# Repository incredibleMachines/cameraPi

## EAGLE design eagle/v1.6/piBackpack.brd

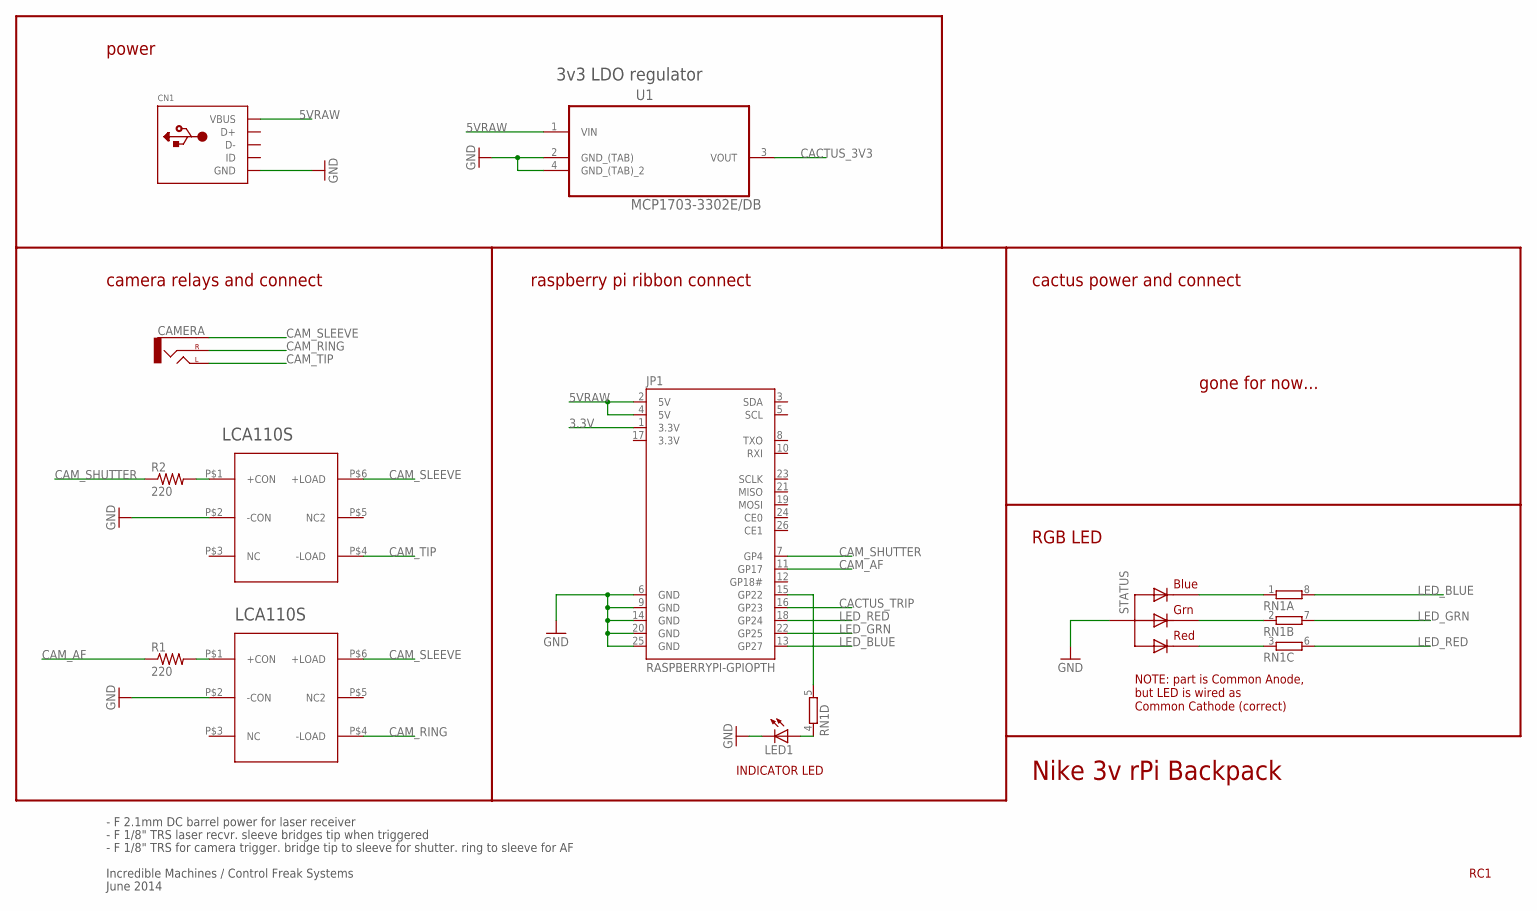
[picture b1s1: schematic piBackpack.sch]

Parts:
CAMERA: AUDIO-JACKPTH; AUDIO-JACK
CN1: USBMOLEX; USB-MINIB-THM-MOLEX
JP1: RASPBERRYPI-GPIOPTH; 2X13-SHROUDED
LCA110S, LCA110S1: LCA110S; 6-SMD
LED1: LED3MM
R1, R2: 220; 0204/5
RN1: 4R-NEXBS8V; EXBS8V
STATUS: RGBLED_CA-5MM; LED5MMRGB
U1: MCP1703-3302E/DB; SOT230P700X180-4N

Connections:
3.3V: JP1.1 (3.3V), JP1.17 (3.3V)
5VRAW: CN1.VBUS, JP1.2 (5V), JP1.4 (5V), U1.1 (VIN)
CACTUS_3V3: U1.3 (VOUT)
CACTUS_TRIP: JP1.16 (GP23)
CAM_AF: JP1.11 (GP17), R1.1
CAM_RING: CAMERA.RING (RIGHT), LCA110S.P$4 (-LOAD)
CAM_SHUTTER: JP1.7 (GP4), R2.1
CAM_SLEEVE: CAMERA.SLEEVE, LCA110S.P$6 (+LOAD), LCA110S1.P$6 (+LOAD)
CAM_TIP: CAMERA.TIP (LEFT), LCA110S1.P$4 (-LOAD)
GND: CN1.GND, JP1.6 (GND), JP1.9 (GND), JP1.14 (GND), JP1.20 (GND), JP1.25 (GND), LCA110S.P$2 (-CON), LCA110S1.P$2 (-CON), LED1.K (C), STATUS.2 (VCC), U1.2 (GND_(TAB)), U1.4 (GND_(TAB)_2)
LED_BLUE: JP1.13 (GP27), RN1.8 (2)
LED_GRN: JP1.22 (GP25), RN1.7 (2)
LED_RED: JP1.18 (GP24), RN1.6 (2)
unnamed: RN1.1, STATUS.4 (BLUE)
unnamed: RN1.2 (1), STATUS.3 (GREEN)
unnamed: RN1.3 (1), STATUS.1 (RED)
unnamed: JP1.15 (GP22), RN1.5 (2)
unnamed: LED1.A, RN1.4 (1)
unnamed: LCA110S.P$1 (+CON), R1.2
unnamed: LCA110S1.P$1 (+CON), R2.2

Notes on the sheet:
Nike 3v rPi Backpack
Incredible Machines / Control Freak Systems
June 2014
- F 2.1mm DC barrel power for laser receiver
- F 1/8" TRS laser recvr. sleeve bridges tip when triggered
- F 1/8" TRS for camera trigger. bridge tip to sleeve for shutter. ring to sleeve for AF
NOTE: part is Common Anode, but LED is wired as Common Cathode (correct)
raspberry pi ribbon connect
camera relays and connect
RGB LED
cactus power and connect
RC1
INDICATOR LED
power
3v3 LDO regulator
LCA110S
gone for now...

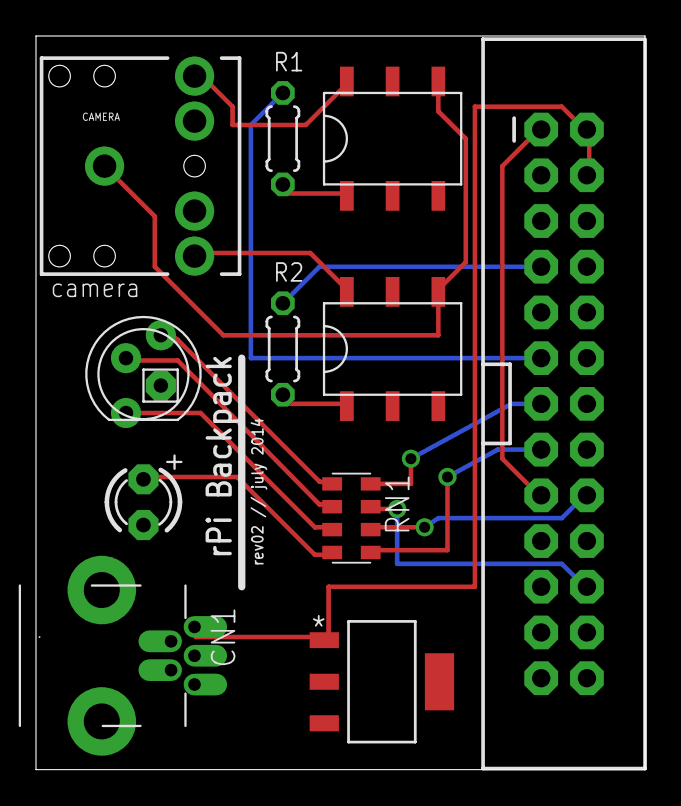
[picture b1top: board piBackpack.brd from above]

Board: 2 copper layers, 33.8 x 40.8 mm, 11 parts (0 on the bottom side), 18 nets.

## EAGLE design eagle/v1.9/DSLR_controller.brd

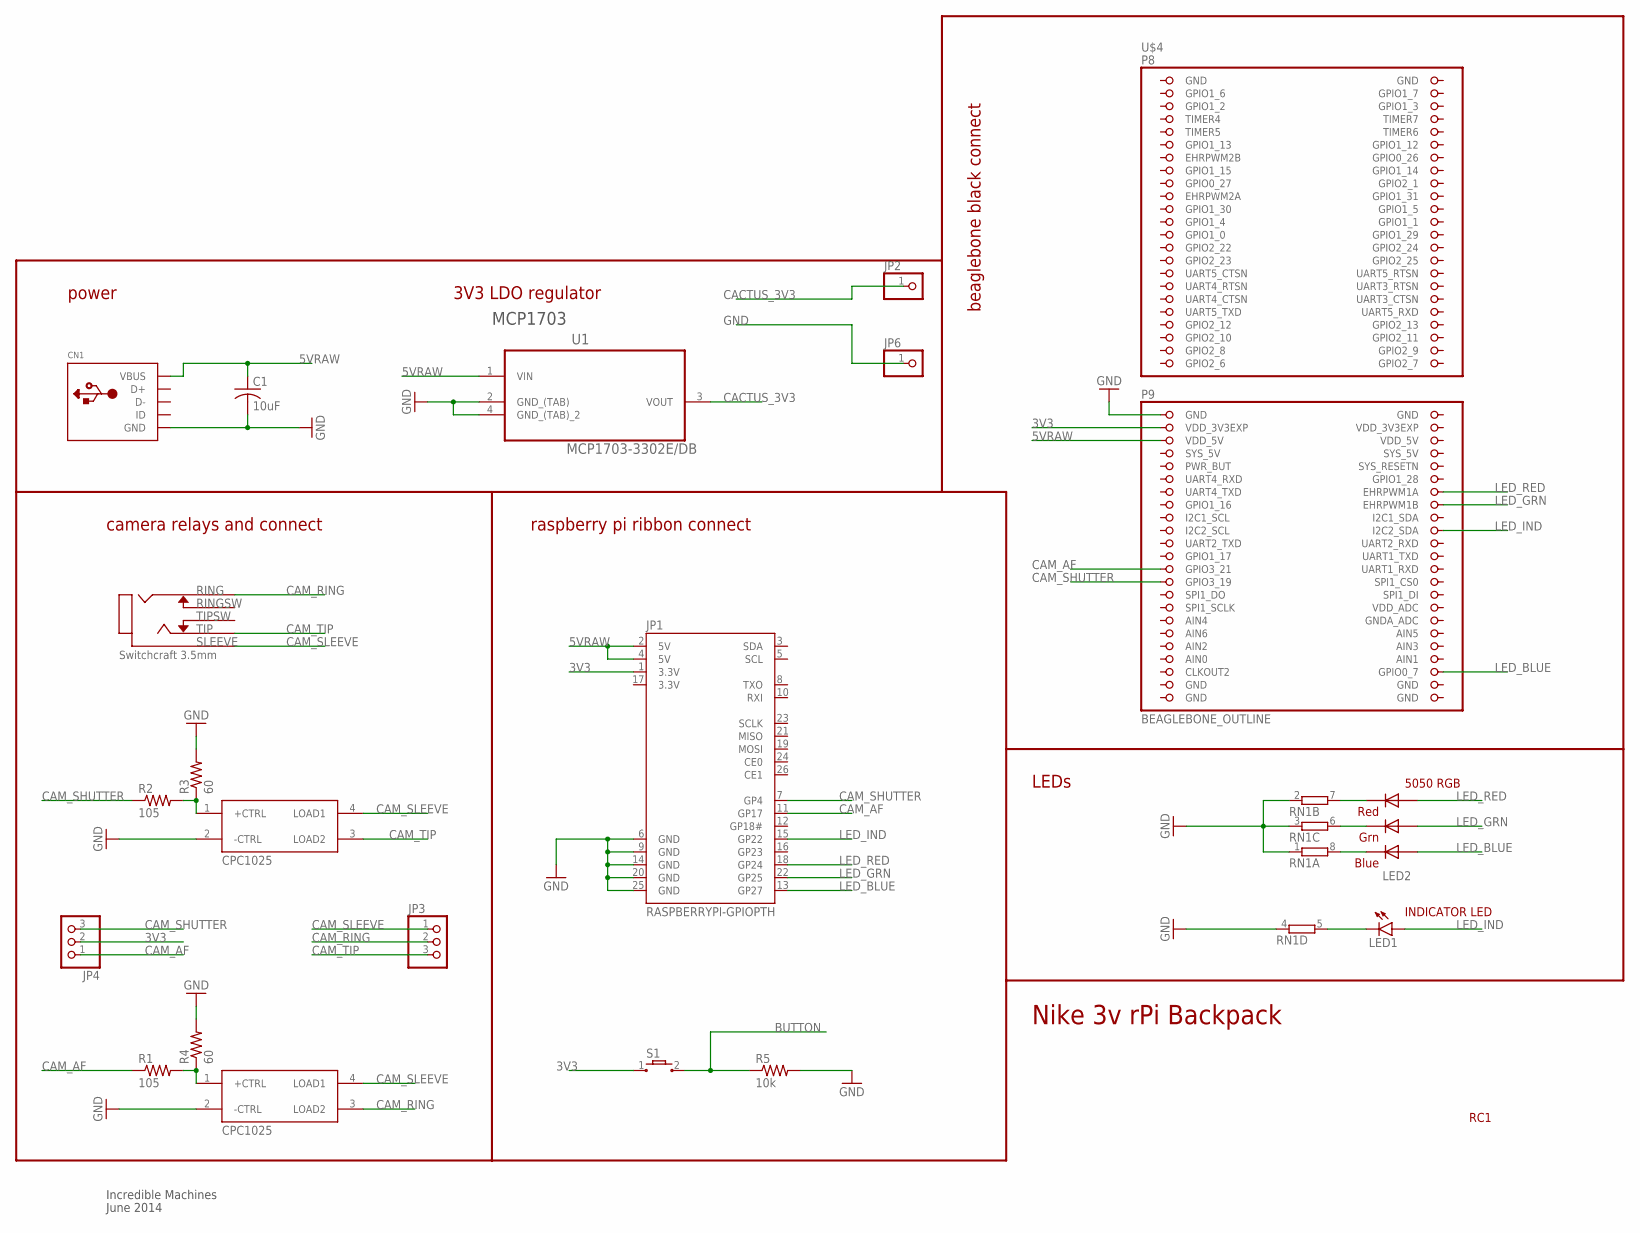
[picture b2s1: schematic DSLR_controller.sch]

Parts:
C1: 10uF; C1206K
CN1: USBMOLEX; USB-MINIB-THM-MOLEX
JP1: RASPBERRYPI-GPIOPTH; 2X13-SHROUDED
JP2, JP6: PINHD-1X1CB; 1X01-CLEANBIG
JP3, JP4: PINHD-1X3CB; 1X03-CLEANBIG
LED1: LED1206; LED-1206
LED2: RGBLED5050
R1, R2: 105; R1206
R3, R4: 60; R1206
R5: 10k; R1206
RN1: 4R-NEXBS8V; EXBS8V
S1: TL3302-G; TL3302_GULL_WING
U1: MCP1703-3302E/DB; SOT230P700X180-4N
U$1: SWTCHCRFT_3.5JACK5-JACK-SMD; 4-JACK-SMD
U$2, U$3: CPC1025_OPTORELAY; 4-OPTORELAY
U$4: BEAGLEBONE_OUTLINE; BEAGLEBONE_SHIELD

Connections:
3.3V: JP1.17 (3.3V)
3V3: JP1.1 (3.3V), JP4.2, S1.1, U$4.49 (VDD_3V3EXP)
5VRAW: C1.1, CN1.VBUS, JP1.2 (5V), JP1.4 (5V), U1.1 (VIN), U$4.51 (VDD_5V)
AIN0: U$4.85 (AIN0)
BUTTON: R5.1, S1.2
CACTUS_3V3: JP2.1, U1.3 (VOUT)
CAM_AF: JP1.11 (GP17), JP4.1, R1.1, U$4.71 (GPIO3_21)
CAM_RING: JP3.2, U$1.2, U$2.3 (LOAD2)
CAM_SHUTTER: JP1.7 (GP4), JP4.3, R2.1, U$4.73 (GPIO3_19)
CAM_SLEEVE: JP3.1, U$1.1, U$2.4 (LOAD1), U$3.4 (LOAD1)
CAM_TIP: JP3.3, U$1.3, U$3.3 (LOAD2)
GND: C1.2, CN1.GND, JP1.6 (GND), JP1.9 (GND), JP1.14 (GND), JP1.20 (GND), JP1.25 (GND), JP6.1, R3.2, R4.2, R5.2, RN1.1, RN1.2 (1), RN1.3 (1), RN1.4 (1), U1.2 (GND_(TAB)), U1.4 (GND_(TAB)_2), U$2.2 (-CTRL), U$3.2 (-CTRL), U$4.1 (GND), U$4.2 (GND), U$4.47 (GND), U$4.48 (GND), U$4.89 (GND), U$4.90 (GND), U$4.91 (GND), U$4.92 (GND)
LED_BLUE: JP1.13 (GP27), LED2.3 (BLUE_A), U$4.88 (GPIO0_7)
LED_GRN: JP1.22 (GP25), LED2.1 (GREEN_A), U$4.62 (EHRPWM1B)
LED_IND: JP1.15 (GP22), LED1.A, U$4.66 (I2C2_SDA)
LED_RED: JP1.18 (GP24), LED2.2 (RED_A), U$4.60 (EHRPWM1A)
unnamed: LED2.6 (GREEN_C), RN1.6 (2)
unnamed: LED2.5 (RED_C), RN1.7 (2)
unnamed: LED2.4 (BLUE_C), RN1.8 (2)
unnamed: LED1.C, RN1.5 (2)
unnamed: R1.2, R4.1, U$2.1 (+CTRL)
unnamed: R2.2, R3.1, U$3.1 (+CTRL)
SYS_5V: U$4.53 (SYS_5V)
VDD_3V3EXP: U$4.50 (VDD_3V3EXP)
VDD_5V: U$4.52 (VDD_5V)

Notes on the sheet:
Nike 3v rPi Backpack
Incredible Machines
June 2014
raspberry pi ribbon connect
camera relays and connect
LEDs
RC1
INDICATOR LED
power
MCP1703
beaglebone black connect
5050 RGB
3V3 LDO regulator

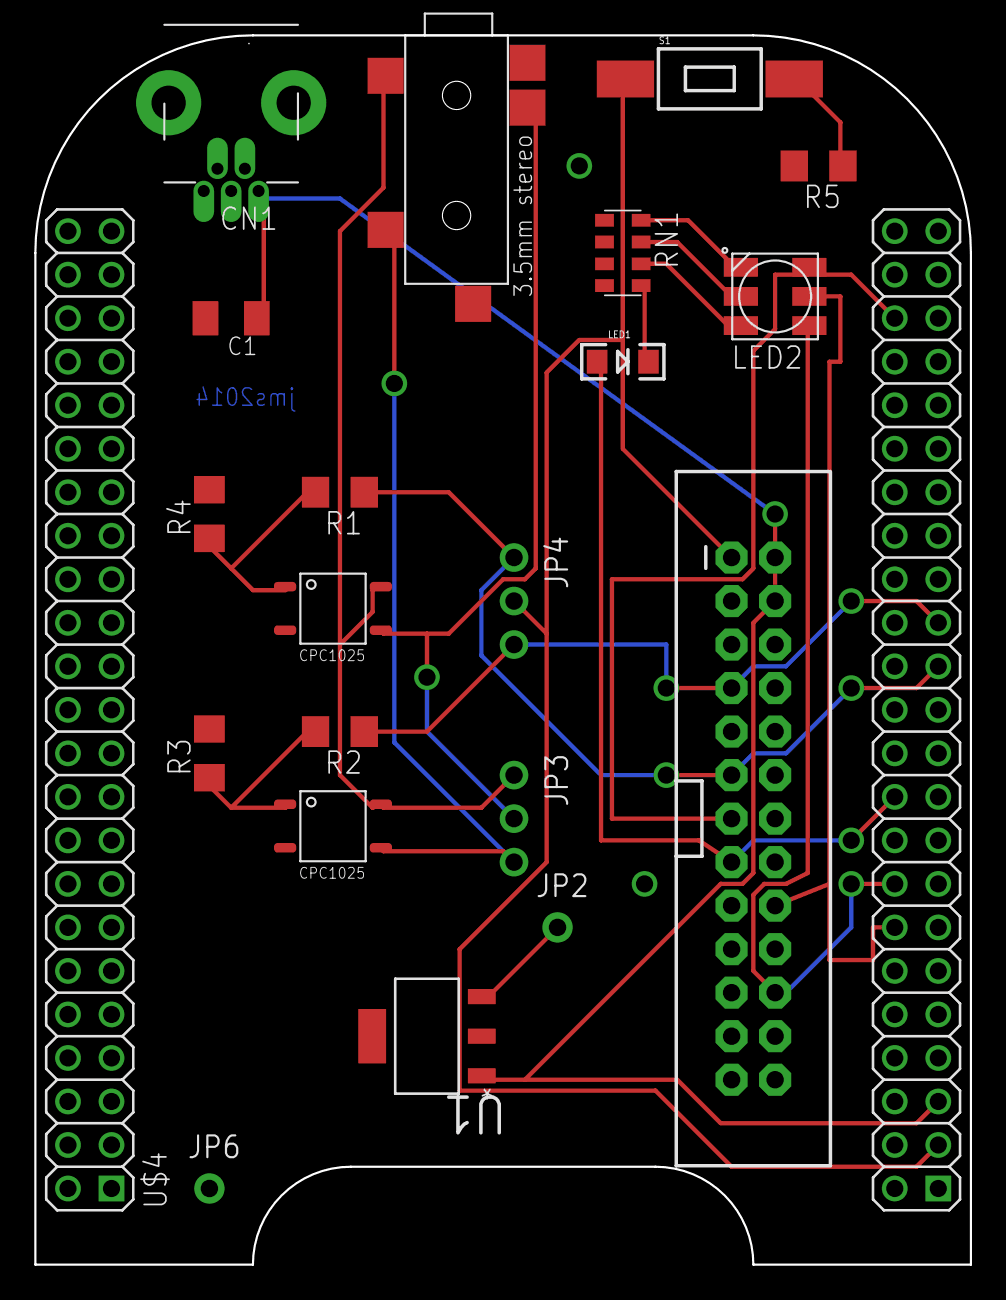
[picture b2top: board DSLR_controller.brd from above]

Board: 2 copper layers, 54.6 x 71.8 mm, 21 parts (0 on the bottom side), 20 nets.

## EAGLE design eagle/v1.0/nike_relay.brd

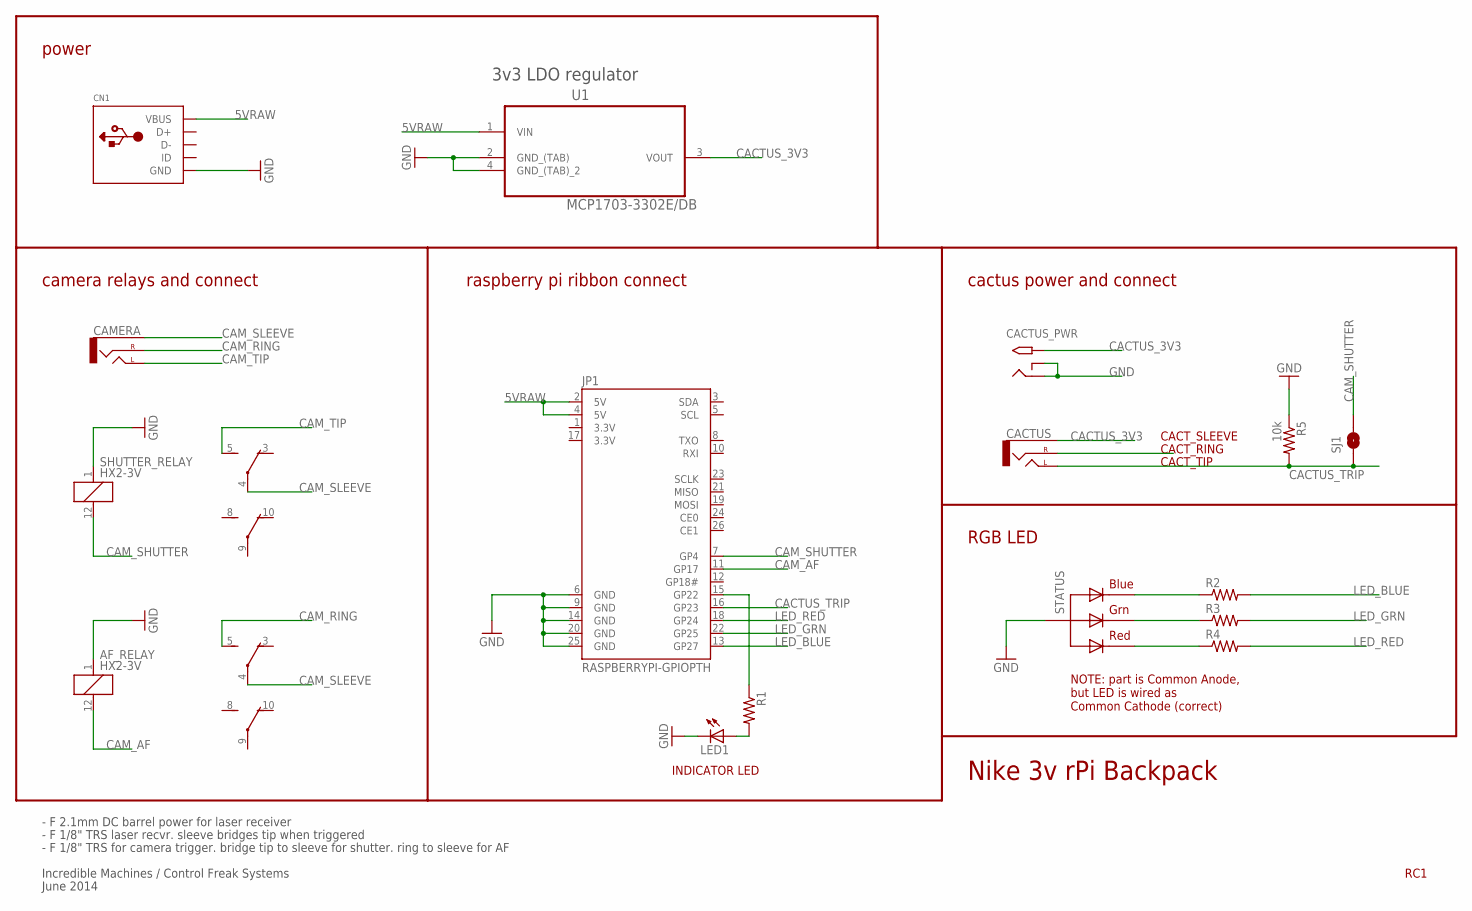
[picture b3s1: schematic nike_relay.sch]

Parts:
AF_RELAY: HX2-3V; HX
CACTUS: AUDIO-JACKPTH; AUDIO-JACK
CACTUS_PWR: 2.1MMJACKTHM; PJ-102A
CAMERA: AUDIO-JACKPTH; AUDIO-JACK
CN1: USBMOLEX; USB-MINIB-THM-MOLEX
JP1: RASPBERRYPI-GPIOPTH; 2X13-SHROUDED
LED1: LED3MM
R1, R2, R3, R4: R-US_0204/5; 0204/5
R5: 10k; 0204/5
SHUTTER_RELAY: HX2-3V; HX
SJ1: SOLDERJUMPER-OLDNO; SJ_2S-NO
STATUS: RGBLED_CA-5MM; LED5MMRGB
U1: MCP1703-3302E/DB; SOT230P700X180-4N

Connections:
3.3V: JP1.1 (3.3V), JP1.17 (3.3V)
5VRAW: CN1.VBUS, JP1.2 (5V), JP1.4 (5V), U1.1 (VIN)
CACTUS_3V3: CACTUS.SLEEVE, CACTUS_PWR.TIP, U1.3 (VOUT)
CACTUS_TRIP: CACTUS.TIP (LEFT), JP1.16 (GP23), R5.2, SJ1.1
CACT_RING: CACTUS.RING (RIGHT)
CAM_AF: AF_RELAY.12 (2), JP1.11 (GP17)
CAM_RING: AF_RELAY.5 (S), CAMERA.RING (RIGHT)
CAM_SHUTTER: JP1.7 (GP4), SHUTTER_RELAY.12 (2), SJ1.2
CAM_SLEEVE: AF_RELAY.4, CAMERA.SLEEVE, SHUTTER_RELAY.4
CAM_TIP: CAMERA.TIP (LEFT), SHUTTER_RELAY.5 (S)
GND: AF_RELAY.1, CACTUS_PWR.RING, CACTUS_PWR.RING_SW, CN1.GND, JP1.6 (GND), JP1.9 (GND), JP1.14 (GND), JP1.20 (GND), JP1.25 (GND), LED1.K (C), R5.1, SHUTTER_RELAY.1, STATUS.2 (VCC), U1.2 (GND_(TAB)), U1.4 (GND_(TAB)_2)
LED_BLUE: JP1.13 (GP27), R2.2
LED_GRN: JP1.22 (GP25), R3.2
LED_RED: JP1.18 (GP24), R4.2
unnamed: R2.1, STATUS.4 (BLUE)
unnamed: R3.1, STATUS.3 (GREEN)
unnamed: R4.1, STATUS.1 (RED)
unnamed: JP1.15 (GP22), R1.1
unnamed: LED1.A, R1.2

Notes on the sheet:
Nike 3v rPi Backpack
Incredible Machines / Control Freak Systems
June 2014
- F 2.1mm DC barrel power for laser receiver
- F 1/8" TRS laser recvr. sleeve bridges tip when triggered
- F 1/8" TRS for camera trigger. bridge tip to sleeve for shutter. ring to sleeve for AF
CACT_SLEEVE
CACT_TIP
CACT_RING
NOTE: part is Common Anode, but LED is wired as Common Cathode (correct)
raspberry pi ribbon connect
camera relays and connect
RGB LED
cactus power and connect
RC1
INDICATOR LED
power
3v3 LDO regulator

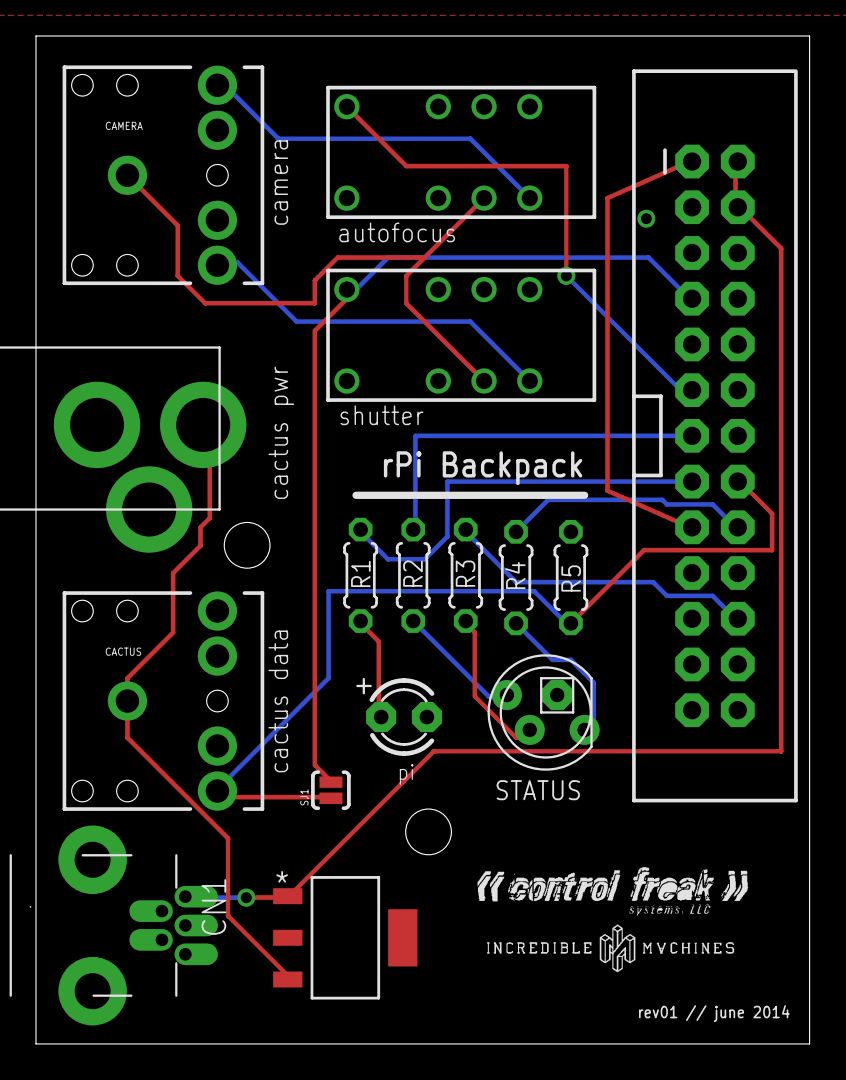
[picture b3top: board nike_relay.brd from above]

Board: 2 copper layers, 43.0 x 56.0 mm, 16 parts (0 on the bottom side), 18 nets.

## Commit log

2014-06-06 Adding Basic ignore strategies
2014-06-06 Adding .gitignore
2014-06-06 Adding all the files
2014-06-07 added all eagle files for rPi backpack
2014-06-07 updating ignore to include .jpg files
2014-06-07 Various Changes still in beta form - image downloading, camera control, gpio functionality
    Beta state for various server implimentations listed below. All these files are super ugly and need lots of work, don't judge.
    CameraControl to sync w. camera via usb and listen for changes in order to capture images and post to download server.
    Download to receive images via express to process and name files as they come into our server.
    Minor mods to gpio2.js
2014-06-07 removing bunk imageDownload folder and package
2014-06-07 removing stupid RTF File
2014-06-07 adding restore instructions, should probably be converted to a readme
2014-06-07 enabling download and trigger apps to run concurrently, modifying camera controls to support this functionality
2014-06-07 created laser prototype folder
2014-06-08 laser functionality proven. run node laser.js to see laser hit shutter pin and light LED when triggered. Trigger buffer time implemented.
2014-06-08 Rearranging folder structures adding camera http server functionality
2014-06-08 reformatting naming of laser trigger
2014-06-08 Initial browser commit App for sending out camera settings
2014-06-08 deleting bunk file
2014-06-08 adding .mov
2014-06-08 removing bunk .mov files
2014-06-08 adding in captureAll.js - a test to try all GPIO pin activity using asynchronous interrupts. package.json now includes onoff package
2014-06-08 Working drop downs for all camera settings
2014-06-08 Adding support for Camera API http server and Capture EOSSerialCapture and report
    This code still needs to test the http posting etc once the browser app is ready to rock. additionally still needs camera wake up functionality
2014-06-08 updated laser.js to use onoff, captureALL test added, packages all include onoff now
2014-06-08 fixing capture to run after get is recieved
2014-06-08 updated capture.js to use the onoff npm and updated package.json to match
2014-06-08 Camera Management
    P C# Please enter the commit message for your changes. Lines starting
2014-06-08 Working Camera naming off MongoDB
2014-06-08 port switch to 80
2014-06-08 I lied, setting back to 3000
2014-06-08 RC2 - pi_code
    all correct IP addresses in (show addys)
    updated camera, capture, laser files, packages
    refactored folders
2014-06-09 updating RC2 with all files
2014-06-09 update capture package
2014-06-09 Arm call /arm posts camera info _id, camera_id, address, serial :wq
2014-06-09 Sending get request for setting camera values
2014-06-09 Sends set and get commands to pi Gets settings on load, sets settings when saved individually
2014-06-09 Working check for ip changes, new serial numbers on camera sign on
2014-06-09 Adding trigger updates to browser api also updating capture to get IP address every time.
2014-06-09 quick fix to limit multiple socket connections
2014-06-09 Working camera settings for testing
2014-06-09 pi_code updates and stablization
2014-06-09 Fixed wrong characters
2014-06-09 updating browser_server ip address
2014-06-09 Fixed http requests
2014-06-09 Changed pi route to '/camera'
2014-06-09 organizing utils folder
2014-06-09 updated camera.js to use GPIO lib to control AF pin for waking the camera up on startup and serialID failure
2014-06-09 updated IP addresses to TRUE IPs, worked on allGpio code
2014-06-09 adding git pull functionality to camera, adding gitpull.sh script
2014-06-09 Updating sh path
2014-06-09 Working database Correct database queries and calls for all timing and camera settings, has laser data in camera object :wq
2014-06-10 updating git pull
2014-06-10 readding camera.js
2014-06-10 camera.js fix
2014-06-10 updated allGpio
2014-06-10 added backpack test app
2014-06-11 Database with final changes
2014-06-11 WIP download app for testing
2014-06-11 updated test backpack code to be dumb simple
2014-06-11 Adding Ping functionality to socket server
2014-06-11 trigger update with ping route
2014-06-11 trigger timing tests
2014-06-11 trying ping pong
2014-06-11 added laser test code
2014-06-12 beginning migration to udp
2014-06-12 Working quad warp Initial commit of working quad warp code, also commit of git pull route to pull ot all pis
2014-06-12 Adding files missed in last commit :wq
2014-06-12 Fixed gitpull onto pis
2014-06-12 WIP Download Mode
2014-06-12 Fixed camel case issue on new info method
2014-06-12 Image Adjustments saving to dbase
2014-06-12 Fixed download folder generation :wq
2014-06-12 WIP processing app
2014-06-12 Changes to browser app on local server
2014-06-12 Initial commit of processing_server Working file naming, warping, cropping, variable framerate encoding, and concat Creates four folders - warped, cropped, movs, output Output stores a file with take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
2014-06-13 Adding in RC4 Candidate from local pi repo with all changes
2014-06-13 "changes to downloads and processing apps for capture
2014-06-13 Changes to browser app for testing
2014-06-13 Working calibration settings saving, checking public folder in downloads for calibration images
2014-06-13 Working calibration public folder setup on processing.js
2014-06-15 Download and Processing Changes Minor changes WIP for calibration mode :wq
2014-06-15 Joined browser and download servers on a single machine :wq
2014-06-15 in processing on mac pro Please enter the commit message for your changes. Lines starting
2014-06-15 Browser and Download Apps
2014-06-15 piFirmware RC5.4
    updated reconnect strategy.
    implemented settings file write when settings are updated.
    laser toggle through udp.
    laser enable and local states are recalled on boot up.
2014-06-15 Final Tait commit on processing app TODO fucking NaN issues!
2014-06-15 Final Tait onsite commit for download/browser machine
2014-06-16 Fixed NaN and crash issues on processing.js Replace recursive file director deleting with library, implemented ffmpeg npm module for creating image sequence (TODO implement for concatenation as well,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
2014-06-16 Fixed render bugs
2014-06-17 adding cameras/all route, cleaning up settings page to correctly write to the pis api
2014-06-17 Changes on image page and processing
2014-06-17 adding settings controller
2014-06-18 important updates to process flow --cp
2014-06-18 merging of scott/chris' code stable browser API, downloads and inits. \n Multi image capture, null image ignore, and lots of other great goodies, enjoy.
2014-06-19 Massive updates to system core, browser, download and processing optimizations, syncing with bolster, spawning multiple takes, takes databasing, controller front end views/app flow, calibration states
2014-06-19 Desktop Commit prior to bringing trashcan online
2014-06-19 Processing Commit prior to bringing trashcan online
2014-06-20 Download optimizations and onite install + New images methods
2014-06-20 Processing rewrite 4:16 AM
2014-06-21 Rewrite of processing for preparing it to move to browser machine
2014-06-21 New image editor
2014-06-22 adding support for ae file creation for beginning of automatic render processing
2014-06-22 confirming sftp curl pull working on system, switching remote route back to correct path
2014-06-22 updating downloads server and downloads server db to send through automation process.
2014-06-23 EOD Commit 6_22, End of render of Sat. clips
2014-06-24 Fully working code pre-tests on night of 6_23
2014-06-27 adding last version of piFirmware to master repo
2014-08-20 added several board revisions

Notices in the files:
parts and their libraries:
SparkFun-Connectors: Licensing: Creative Commons ShareAlike 4.0 International - https://creativecommons.org/licenses/by-sa/4.0
